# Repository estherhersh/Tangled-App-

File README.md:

# Tangled-App-
App for entangled necklaces

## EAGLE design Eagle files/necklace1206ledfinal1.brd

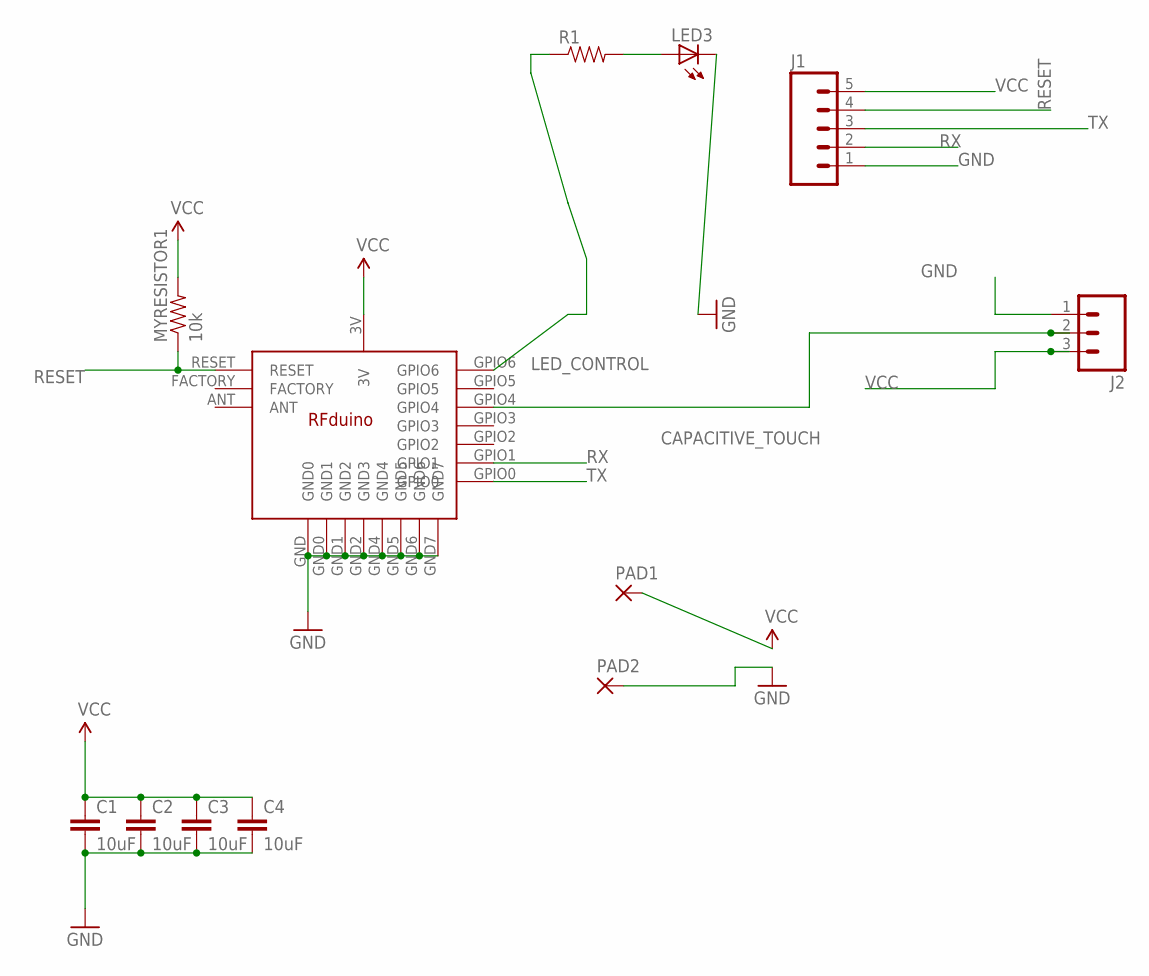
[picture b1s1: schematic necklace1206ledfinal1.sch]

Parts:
C1, C2, C3, C4: 10uF; 0603-CAP
J1: M05PTH_LONGPADS; 1X05_LONGPADS
J2: M03LOCK_LONGPADS; 1X03_LOCK_LONGPADS
LED3: LEDSMT1206; 1206
MYRESISTOR1: 10k; 0603-RES
PAD1, PAD2: 3,81/1,4
R1: RESISTOR0603; 0603-RES
U$2: RFDUINO

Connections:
CAPACITIVE_TOUCH: J2.2, U$2.GPIO4
GND: C1.2, C2.2, C3.2, C4.2, J1.1, J2.1, LED3.C, PAD2.1, U$2.GND (GND0), U$2.GND0 (GND1), U$2.GND1 (GND2), U$2.GND2 (GND3), U$2.GND4, U$2.GND5, U$2.GND6, U$2.GND7
LED_CONTROL: R1.1, U$2.GPIO6
unnamed: LED3.A, R1.2
RESET: J1.4, MYRESISTOR1.1, U$2.RESET
RX: J1.2, U$2.GPIO1
TX: J1.3, U$2.GPIO0
VCC: C1.1, C2.1, C3.1, C4.1, J1.5, J2.3, MYRESISTOR1.2, PAD1.1, U$2.3V

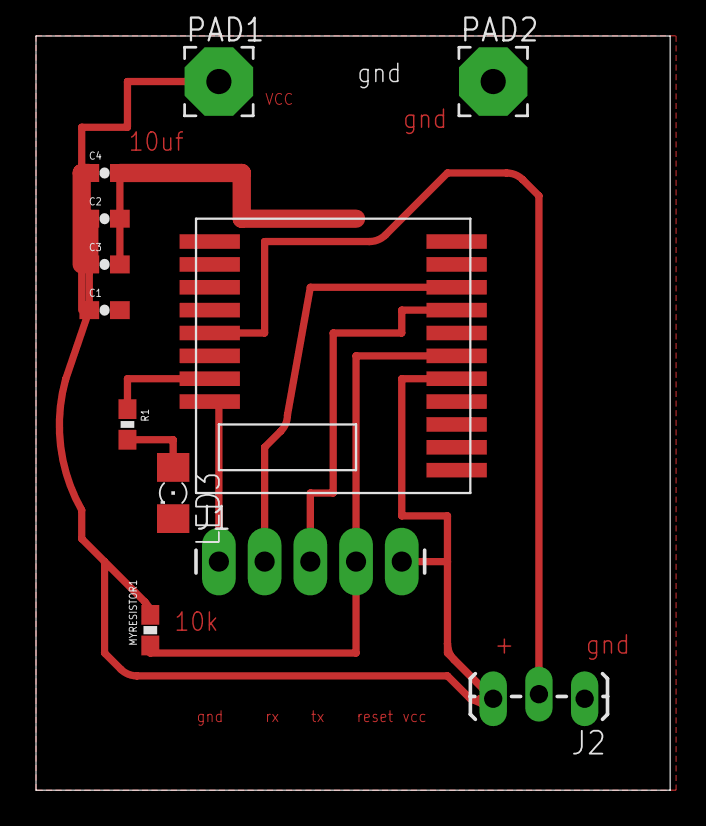
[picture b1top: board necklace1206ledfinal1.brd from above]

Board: 2 copper layers, 35.2 x 41.9 mm, 12 parts (0 on the bottom side), 8 nets.

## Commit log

2017-09-04 working proto
2017-09-04 eagle files added

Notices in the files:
parts and their libraries:
SparkFun-Connectors: Licensing: Creative Commons ShareAlike 4.0 International - https://creativecommons.org/licenses/by-sa/4.0
